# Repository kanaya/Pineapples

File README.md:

# Pineapples
Monorepo for Pineapple Series

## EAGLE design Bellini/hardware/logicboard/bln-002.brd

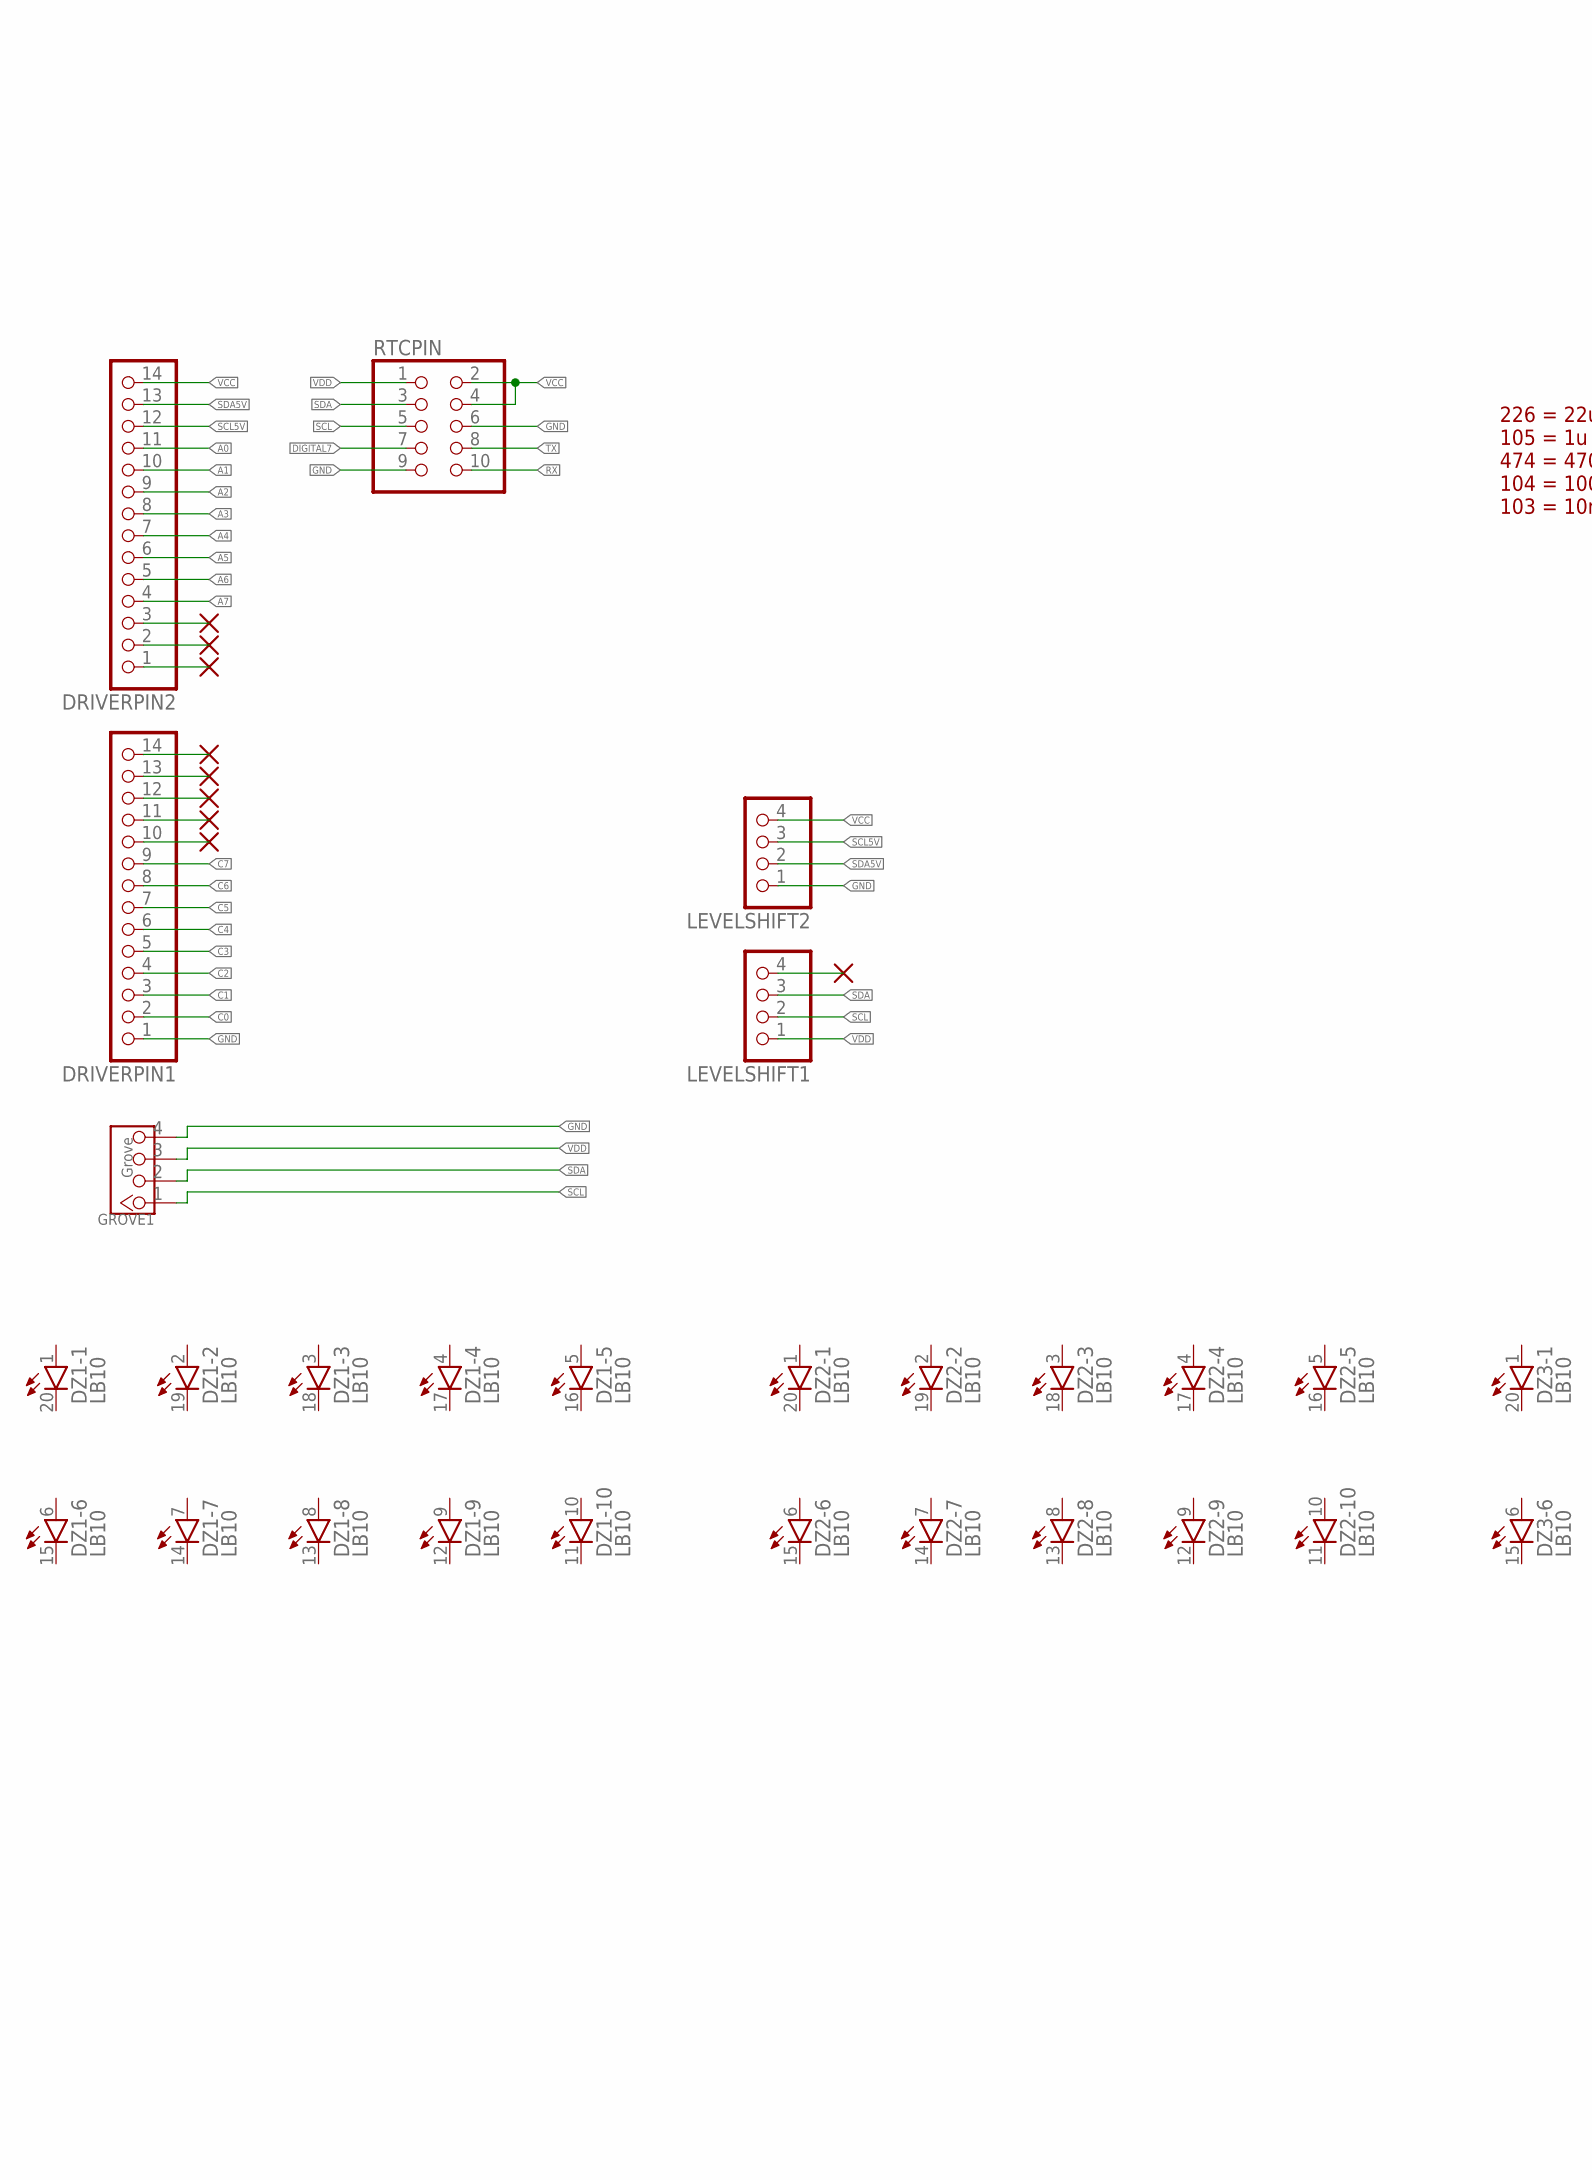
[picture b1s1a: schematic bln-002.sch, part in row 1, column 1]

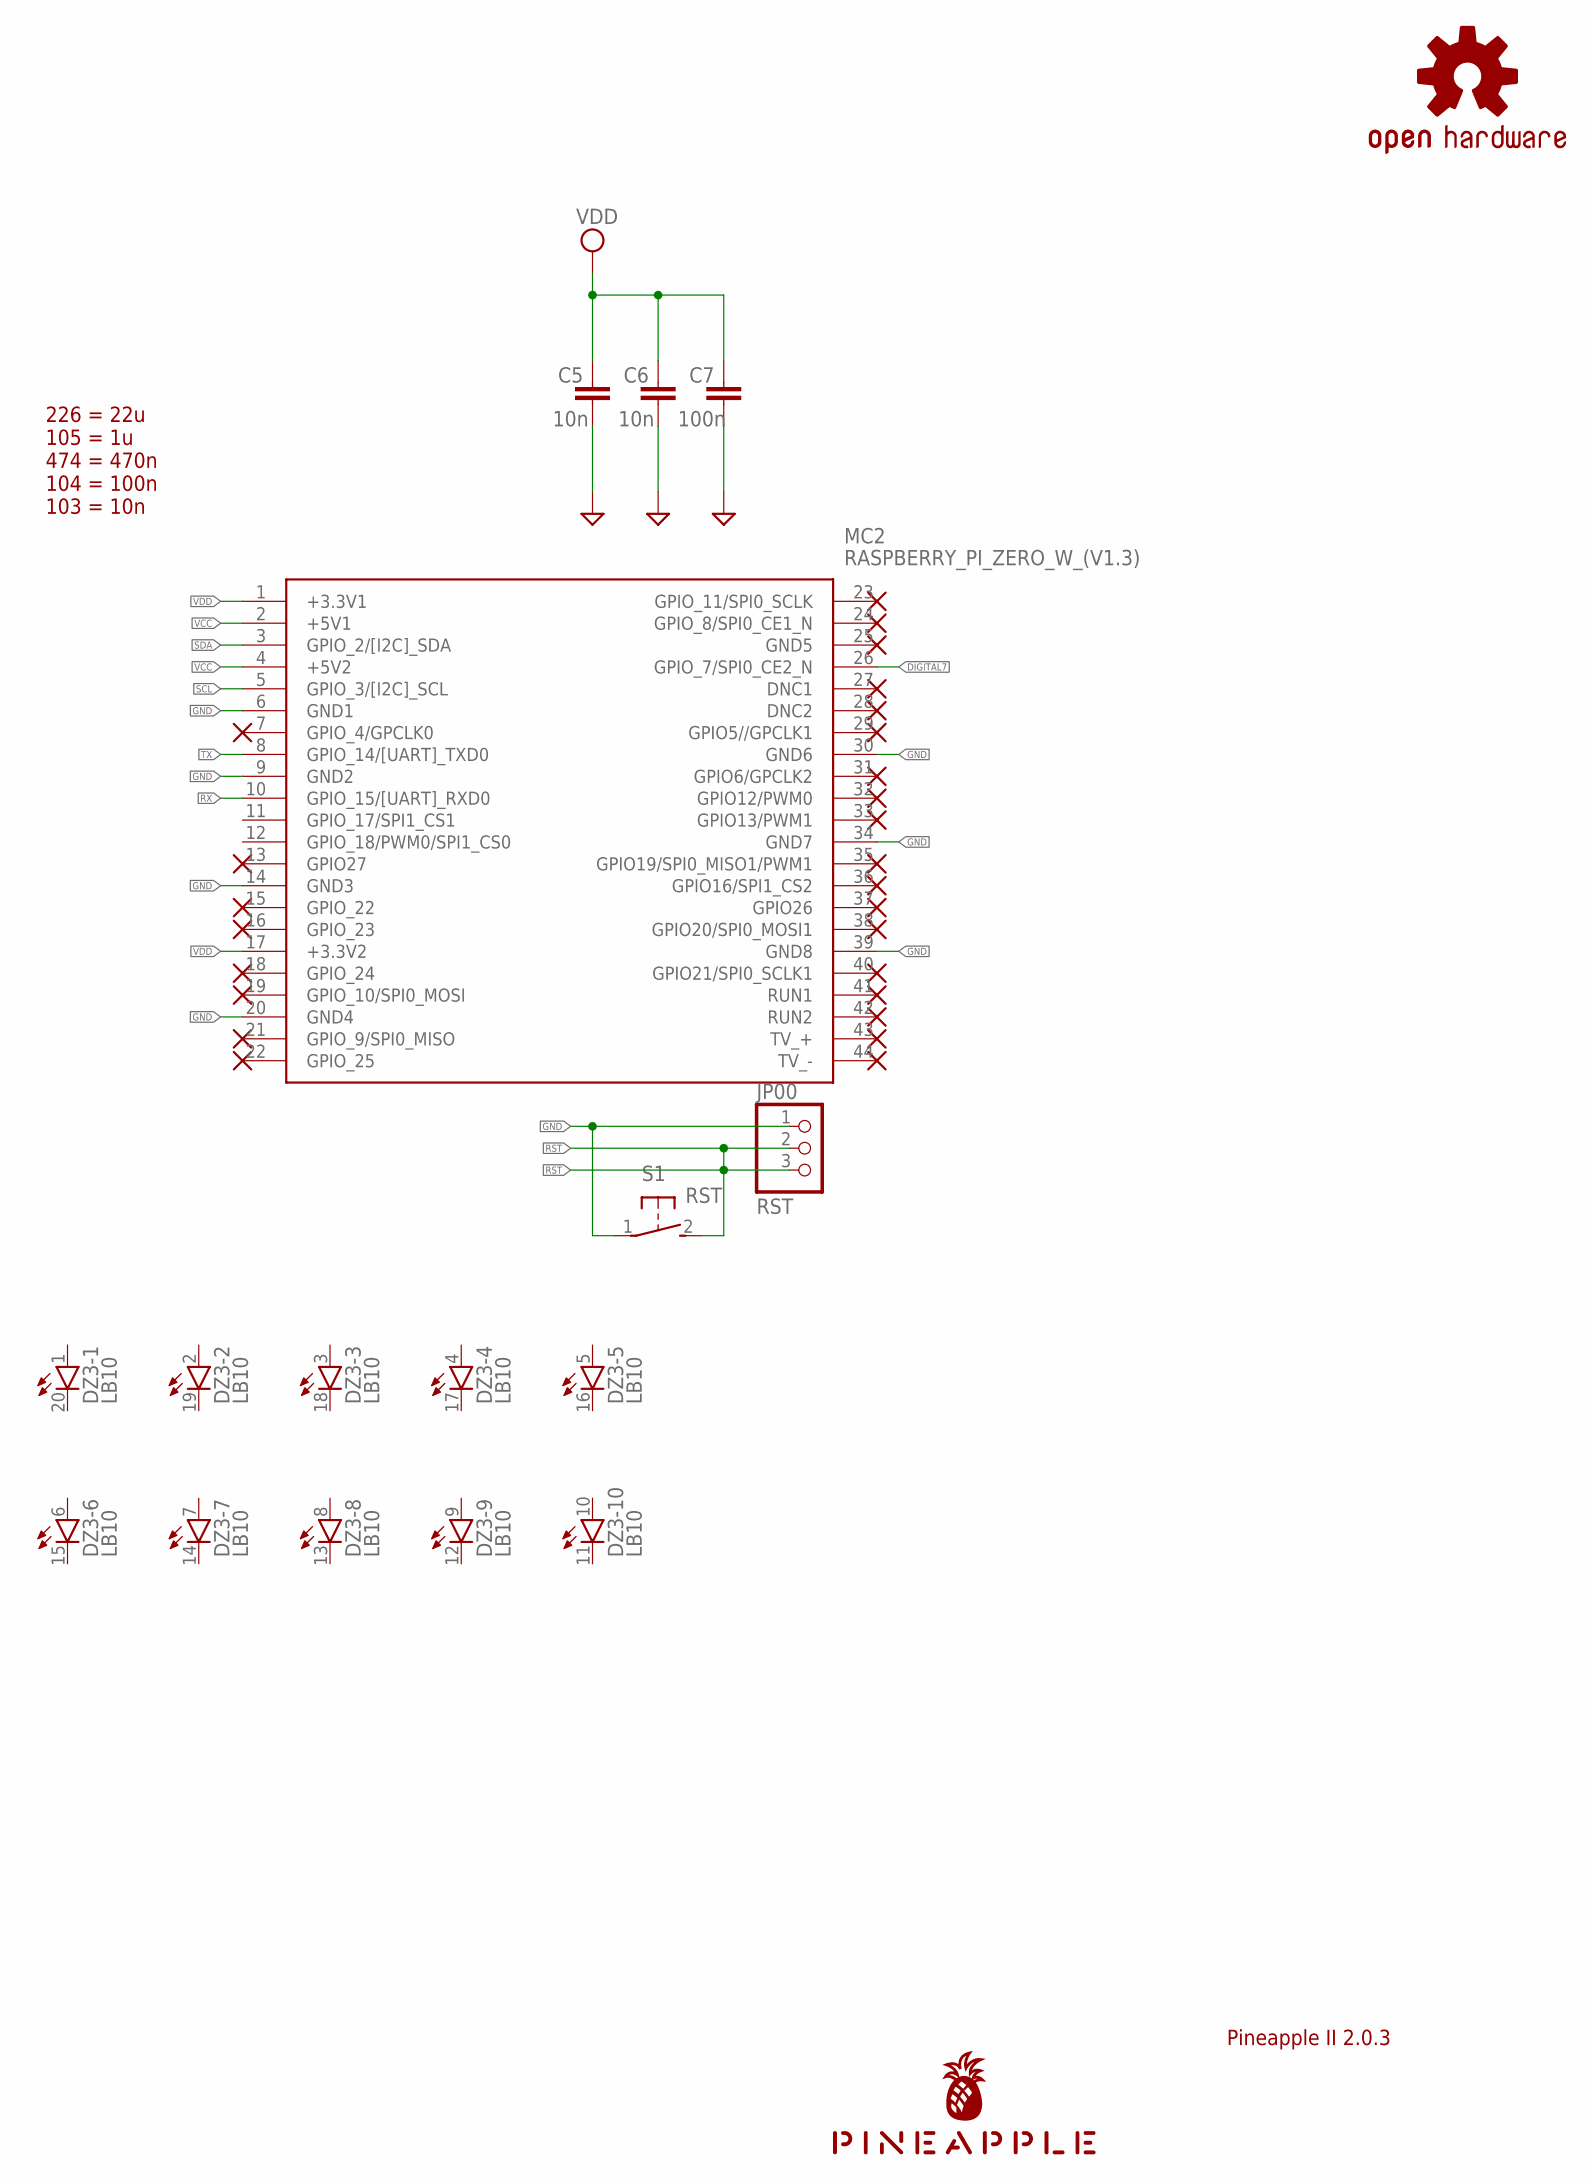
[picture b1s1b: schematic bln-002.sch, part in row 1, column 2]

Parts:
C5, C6: 10n; C025-024X044
C7: 100n; C025-024X044
DRIVERPIN1, DRIVERPIN2: PINHD-1X14; 1X14
DZ1, DZ2, DZ3: LB10
GROVE1: Grove; 4P-2.0-90D
JP00: RST; 1X03
LEVELSHIFT1, LEVELSHIFT2: PINHD-1X4; 1X04
LOGO1: OSHW-LOGOS-COPPER; OSHW-LOGO-S_COPPER
MC2: RASPBERRY_PI_ZERO_W_(V1.3); RASPBERRYPIZEROWV13
RTCPIN: PINHD-2X5; 2X05
S1: RST; B3F-31XX
U$1: PINEAPPLE450_SILK

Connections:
A0: DRIVERPIN2.11
A1: DRIVERPIN2.10
A2: DRIVERPIN2.9
A3: DRIVERPIN2.8
A4: DRIVERPIN2.7
A5: DRIVERPIN2.6
A6: DRIVERPIN2.5
A7: DRIVERPIN2.4
C0: DRIVERPIN1.2
C1: DRIVERPIN1.3
C2: DRIVERPIN1.4
C3: DRIVERPIN1.5
C4: DRIVERPIN1.6
C5: DRIVERPIN1.7
C6: DRIVERPIN1.8
C7: DRIVERPIN1.9
DIGITAL7: MC2.26 (GPIO_7/SPI0_CE2_N), RTCPIN.7
GND: C5.2, C6.2, C7.2, DRIVERPIN1.1, GROVE1.4, JP00.1, LEVELSHIFT2.1, MC2.6 (GND1), MC2.9 (GND2), MC2.14 (GND3), MC2.20 (GND4), MC2.30 (GND6), MC2.34 (GND7), MC2.39 (GND8), RTCPIN.6, RTCPIN.9, S1.1
RST: JP00.2, JP00.3, S1.2 (S)
RX: MC2.10 (GPIO_15/[UART]_RXD0), RTCPIN.10
SCL: GROVE1.1, LEVELSHIFT1.2, MC2.5 (GPIO_3/[I2C]_SCL), RTCPIN.5
SCL5V: DRIVERPIN2.12, LEVELSHIFT2.3
SDA: GROVE1.2, LEVELSHIFT1.3, MC2.3 (GPIO_2/[I2C]_SDA), RTCPIN.3
SDA5V: DRIVERPIN2.13, LEVELSHIFT2.2
TX: MC2.8 (GPIO_14/[UART]_TXD0), RTCPIN.8
VCC: DRIVERPIN2.14, LEVELSHIFT2.4, MC2.2 (+5V1), MC2.4 (+5V2), RTCPIN.2, RTCPIN.4
VDD: C5.1, C6.1, C7.1, GROVE1.3, LEVELSHIFT1.1, MC2.1 (+3.3V1), MC2.17 (+3.3V2), RTCPIN.1

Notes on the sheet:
Pineapple II 2.0.3
226 = 22u 105 = 1u 474 = 470n 104 = 100n 103 = 10n

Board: 2 copper layers, 17 parts (2 on the bottom side), 11 nets, no tracks yet.

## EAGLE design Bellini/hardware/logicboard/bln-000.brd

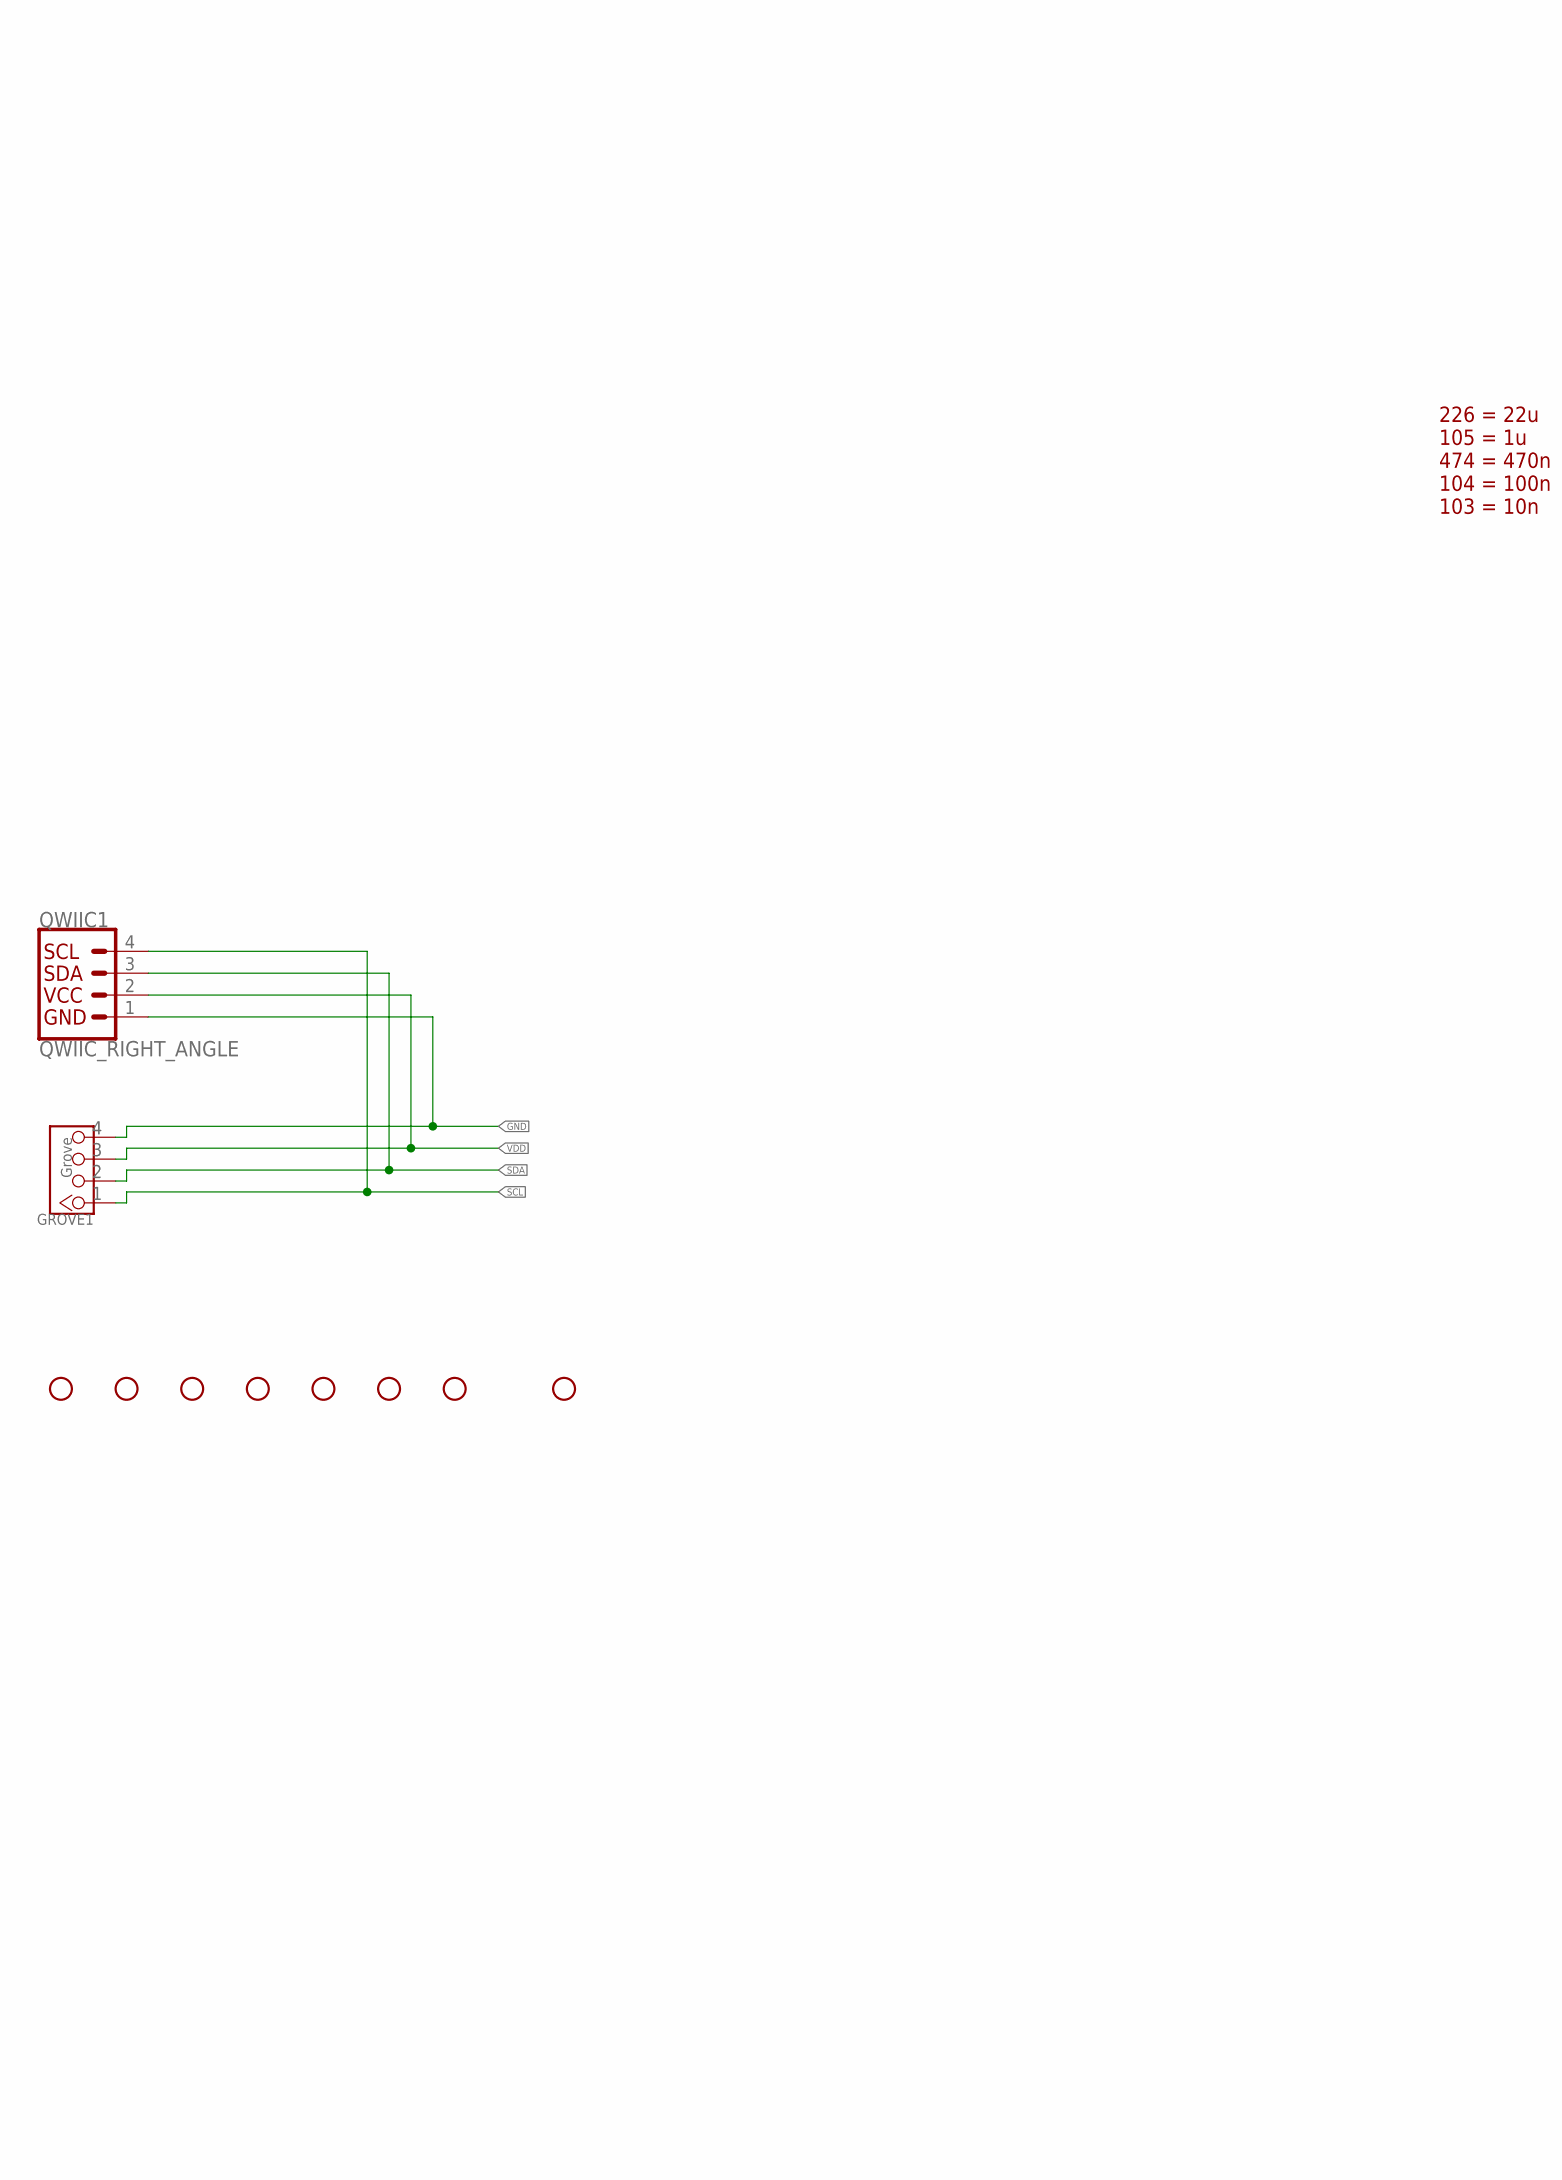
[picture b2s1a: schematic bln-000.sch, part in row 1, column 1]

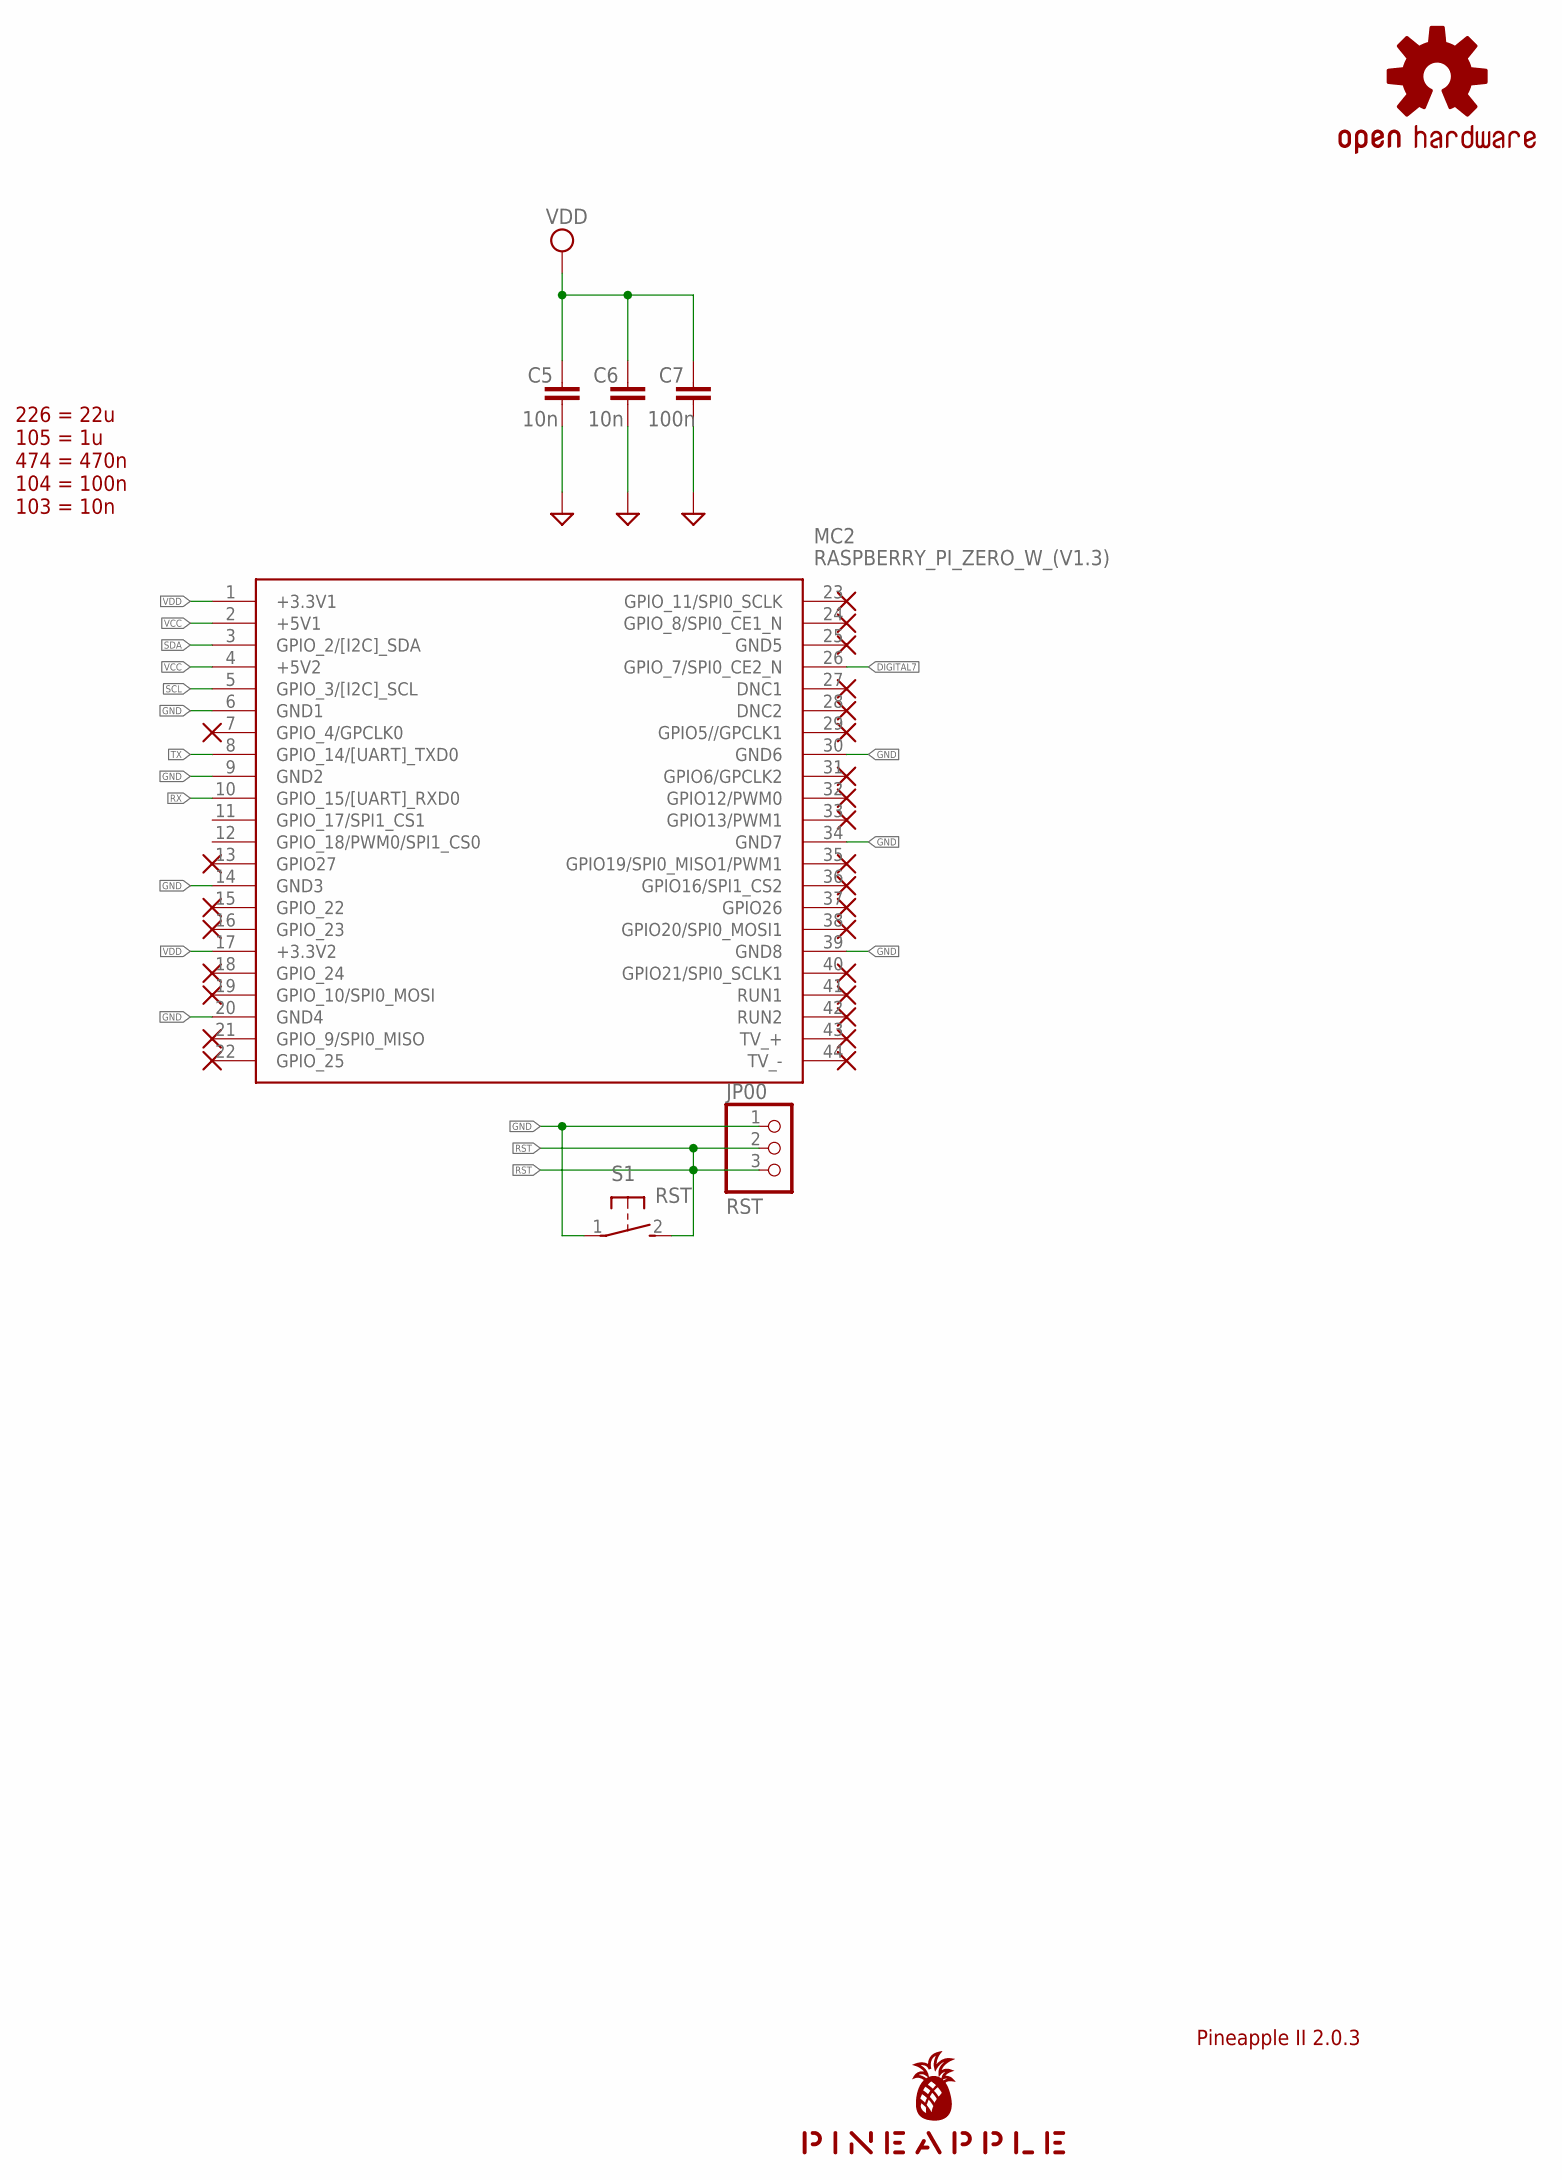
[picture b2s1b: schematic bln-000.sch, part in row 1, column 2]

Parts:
C5, C6: 10n; C025-024X044
C7: 100n; C025-024X044
GROVE1: Grove; 4P-2.0-90D
H1, H2, H3, H4, H5, H6, H7, H8: STAND-OFF
JP00: RST; 1X03
LOGO1: OSHW-LOGOS-COPPER; OSHW-LOGO-S_COPPER
MC2: RASPBERRY_PI_ZERO_W_(V1.3); RASPBERRYPIZEROWV13
QWIIC1: QWIIC_RIGHT_ANGLE; JST04_1MM_RA
S1: RST; B3F-31XX
U$1: PINEAPPLE450_SILK

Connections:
DIGITAL7: MC2.26 (GPIO_7/SPI0_CE2_N)
GND: C5.2, C6.2, C7.2, GROVE1.4, JP00.1, MC2.6 (GND1), MC2.9 (GND2), MC2.14 (GND3), MC2.20 (GND4), MC2.30 (GND6), MC2.34 (GND7), MC2.39 (GND8), QWIIC1.1, S1.1
RST: JP00.2, JP00.3, S1.2 (S)
RX: MC2.10 (GPIO_15/[UART]_RXD0)
SCL: GROVE1.1, MC2.5 (GPIO_3/[I2C]_SCL), QWIIC1.4
SDA: GROVE1.2, MC2.3 (GPIO_2/[I2C]_SDA), QWIIC1.3
TX: MC2.8 (GPIO_14/[UART]_TXD0)
VCC: MC2.2 (+5V1), MC2.4 (+5V2)
VDD: C5.1, C6.1, C7.1, GROVE1.3, MC2.1 (+3.3V1), MC2.17 (+3.3V2), QWIIC1.2

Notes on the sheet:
Pineapple II 2.0.3
226 = 22u 105 = 1u 474 = 470n 104 = 100n 103 = 10n

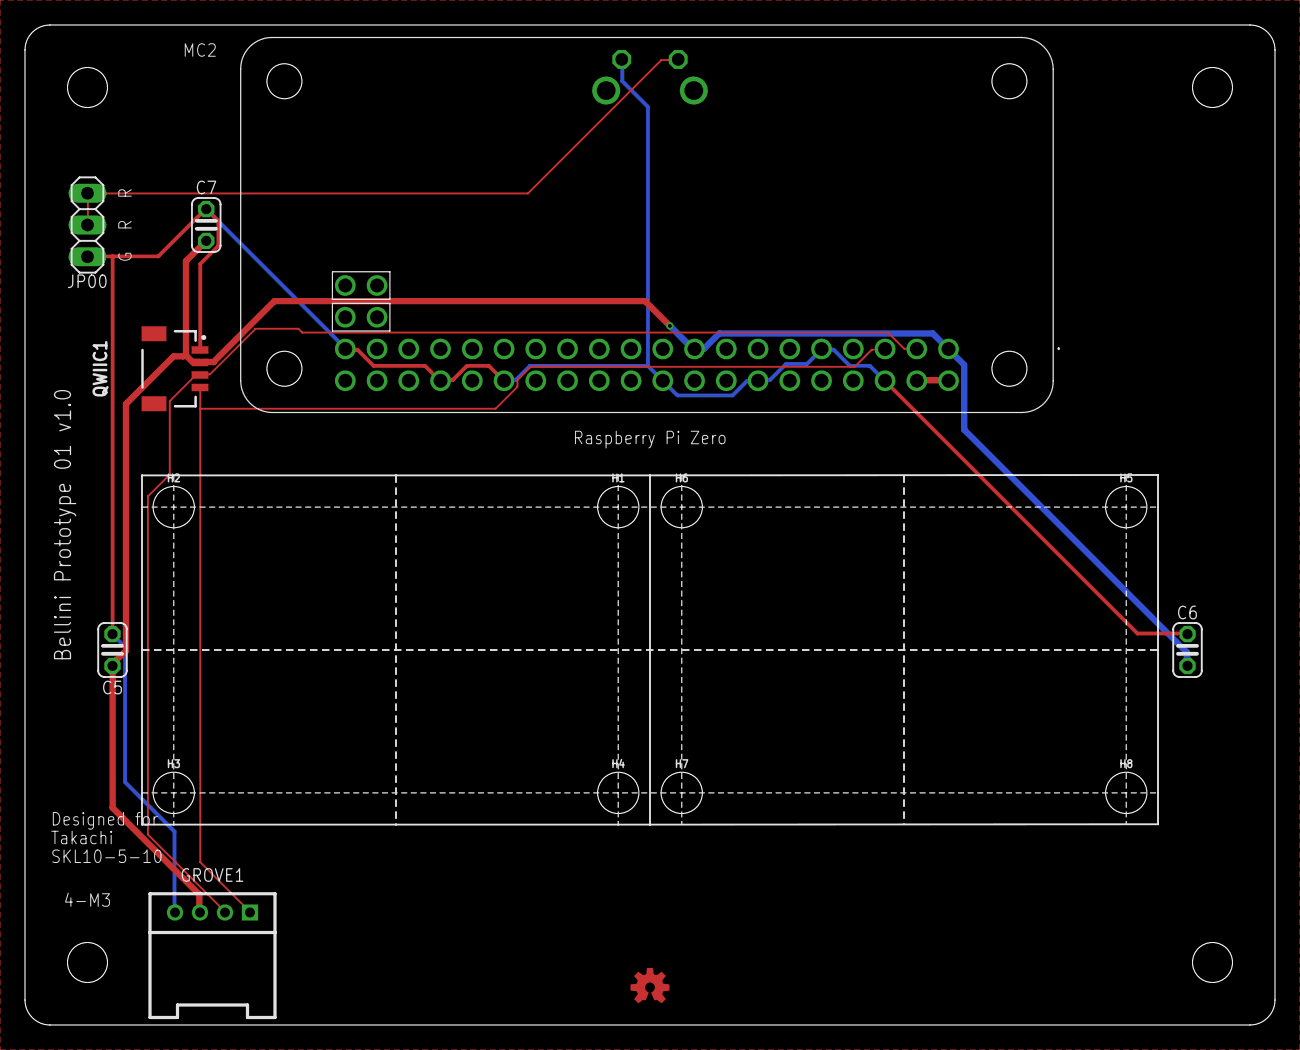
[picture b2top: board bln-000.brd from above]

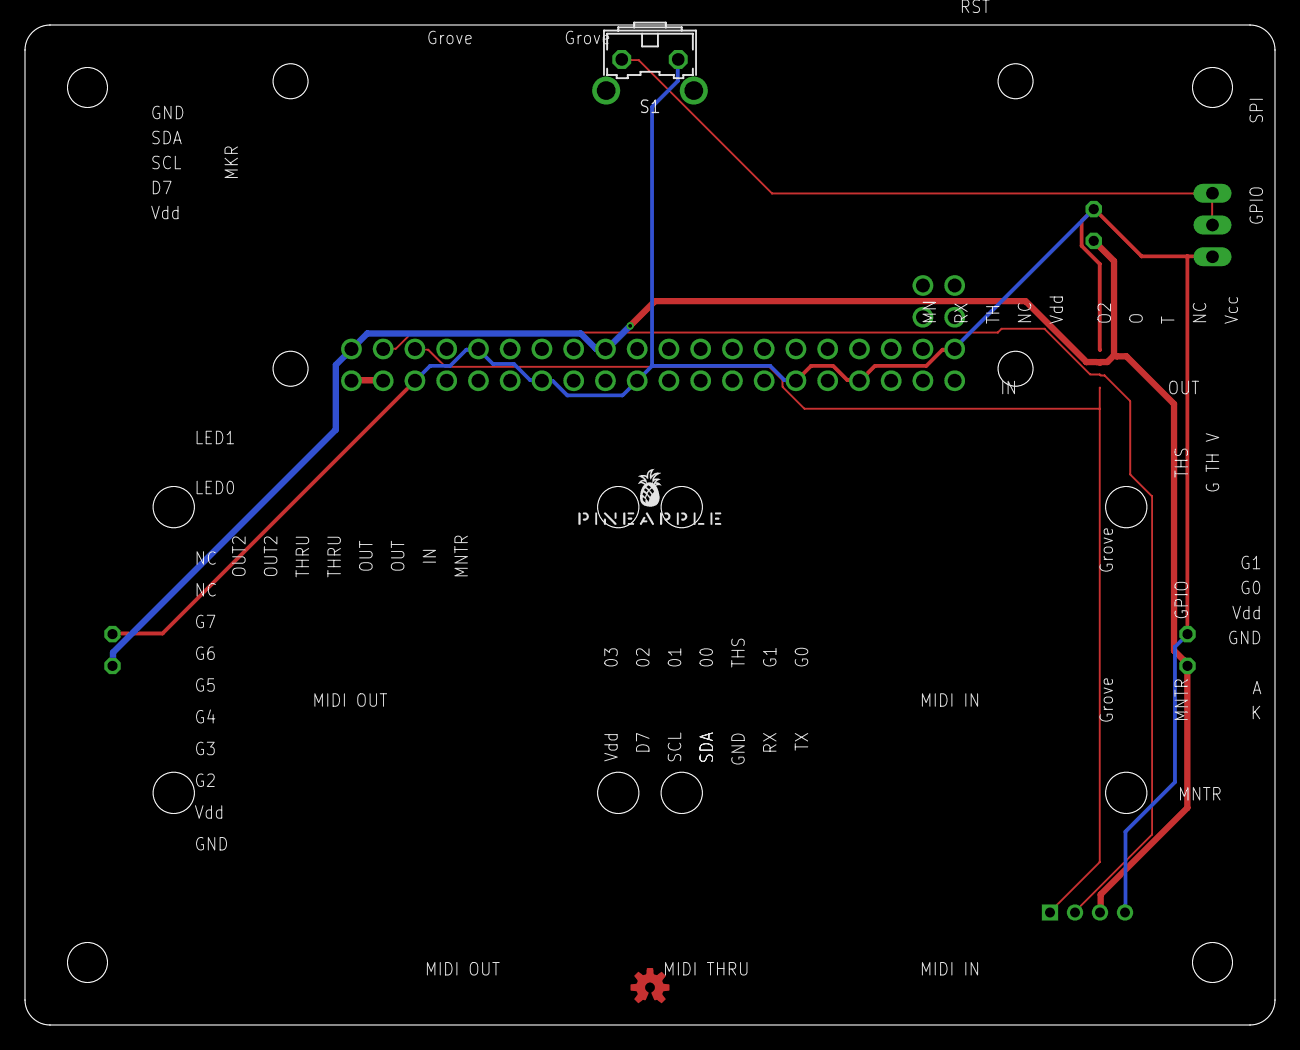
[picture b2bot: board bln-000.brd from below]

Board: 2 copper layers, 100.0 x 80.0 mm, 18 parts (2 on the bottom side), 6 nets.

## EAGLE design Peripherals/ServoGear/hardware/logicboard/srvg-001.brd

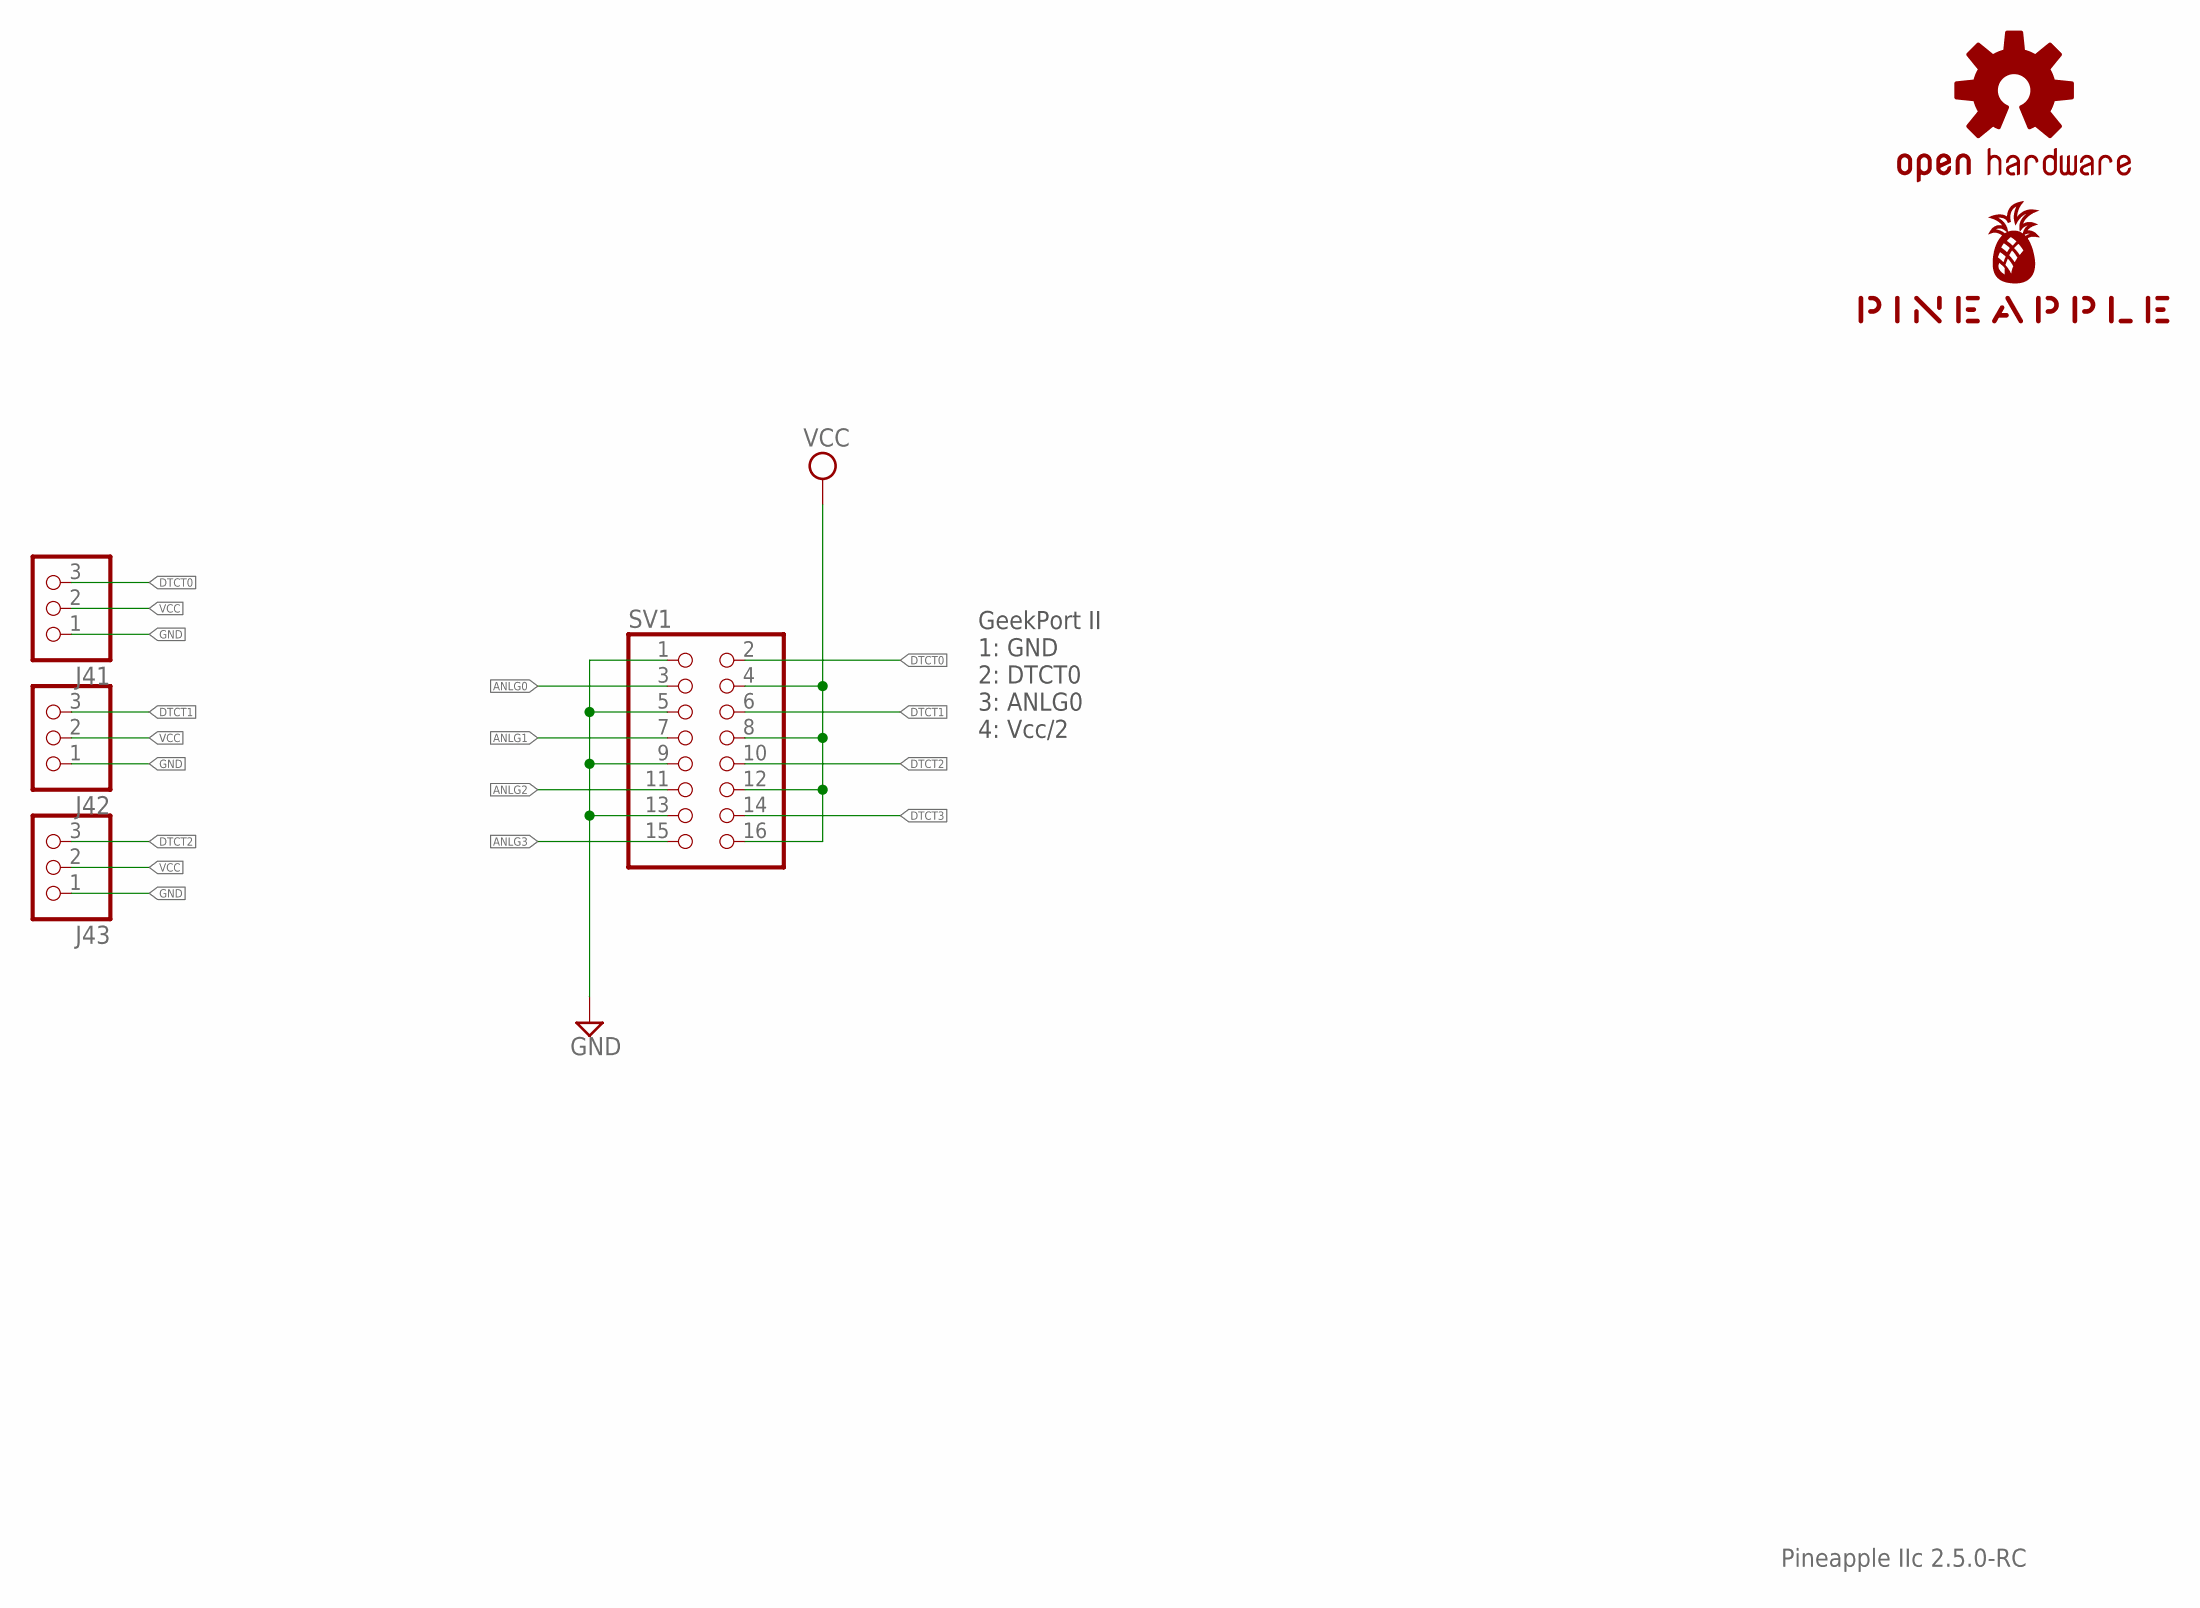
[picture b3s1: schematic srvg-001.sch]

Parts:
J41, J42, J43: PINHD-1X3; 1X03
LOGO1: OSHW-LOGOS-COPPER; OSHW-LOGO-S_COPPER
SV1: PINHD-2X8; 2X08
U$1: PINEAPPLE450_SILK

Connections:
ANLG0: SV1.3
ANLG1: SV1.7
ANLG2: SV1.11
ANLG3: SV1.15
DTCT0: J41.3, SV1.2
DTCT1: J42.3, SV1.6
DTCT2: J43.3, SV1.10
DTCT3: SV1.14
GND: J41.1, J42.1, J43.1, SV1.1, SV1.5, SV1.9, SV1.13
VCC: J41.2, J42.2, J43.2, SV1.4, SV1.8, SV1.12, SV1.16

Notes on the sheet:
Pineapple IIc 2.5.0-RC
GeekPort II 1: GND 2: DTCT0 3: ANLG0 4: Vcc/2

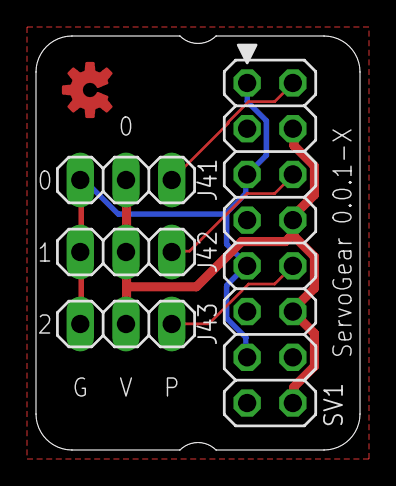
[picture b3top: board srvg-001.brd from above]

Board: 2 copper layers, 18.0 x 23.0 mm, 6 parts (1 on the bottom side), 5 nets.

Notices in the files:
parts and their libraries:
SparkFun-Aesthetics: Licensing: Creative Commons ShareAlike 4.0 International - https://creativecommons.org/licenses/by-sa/4.0
